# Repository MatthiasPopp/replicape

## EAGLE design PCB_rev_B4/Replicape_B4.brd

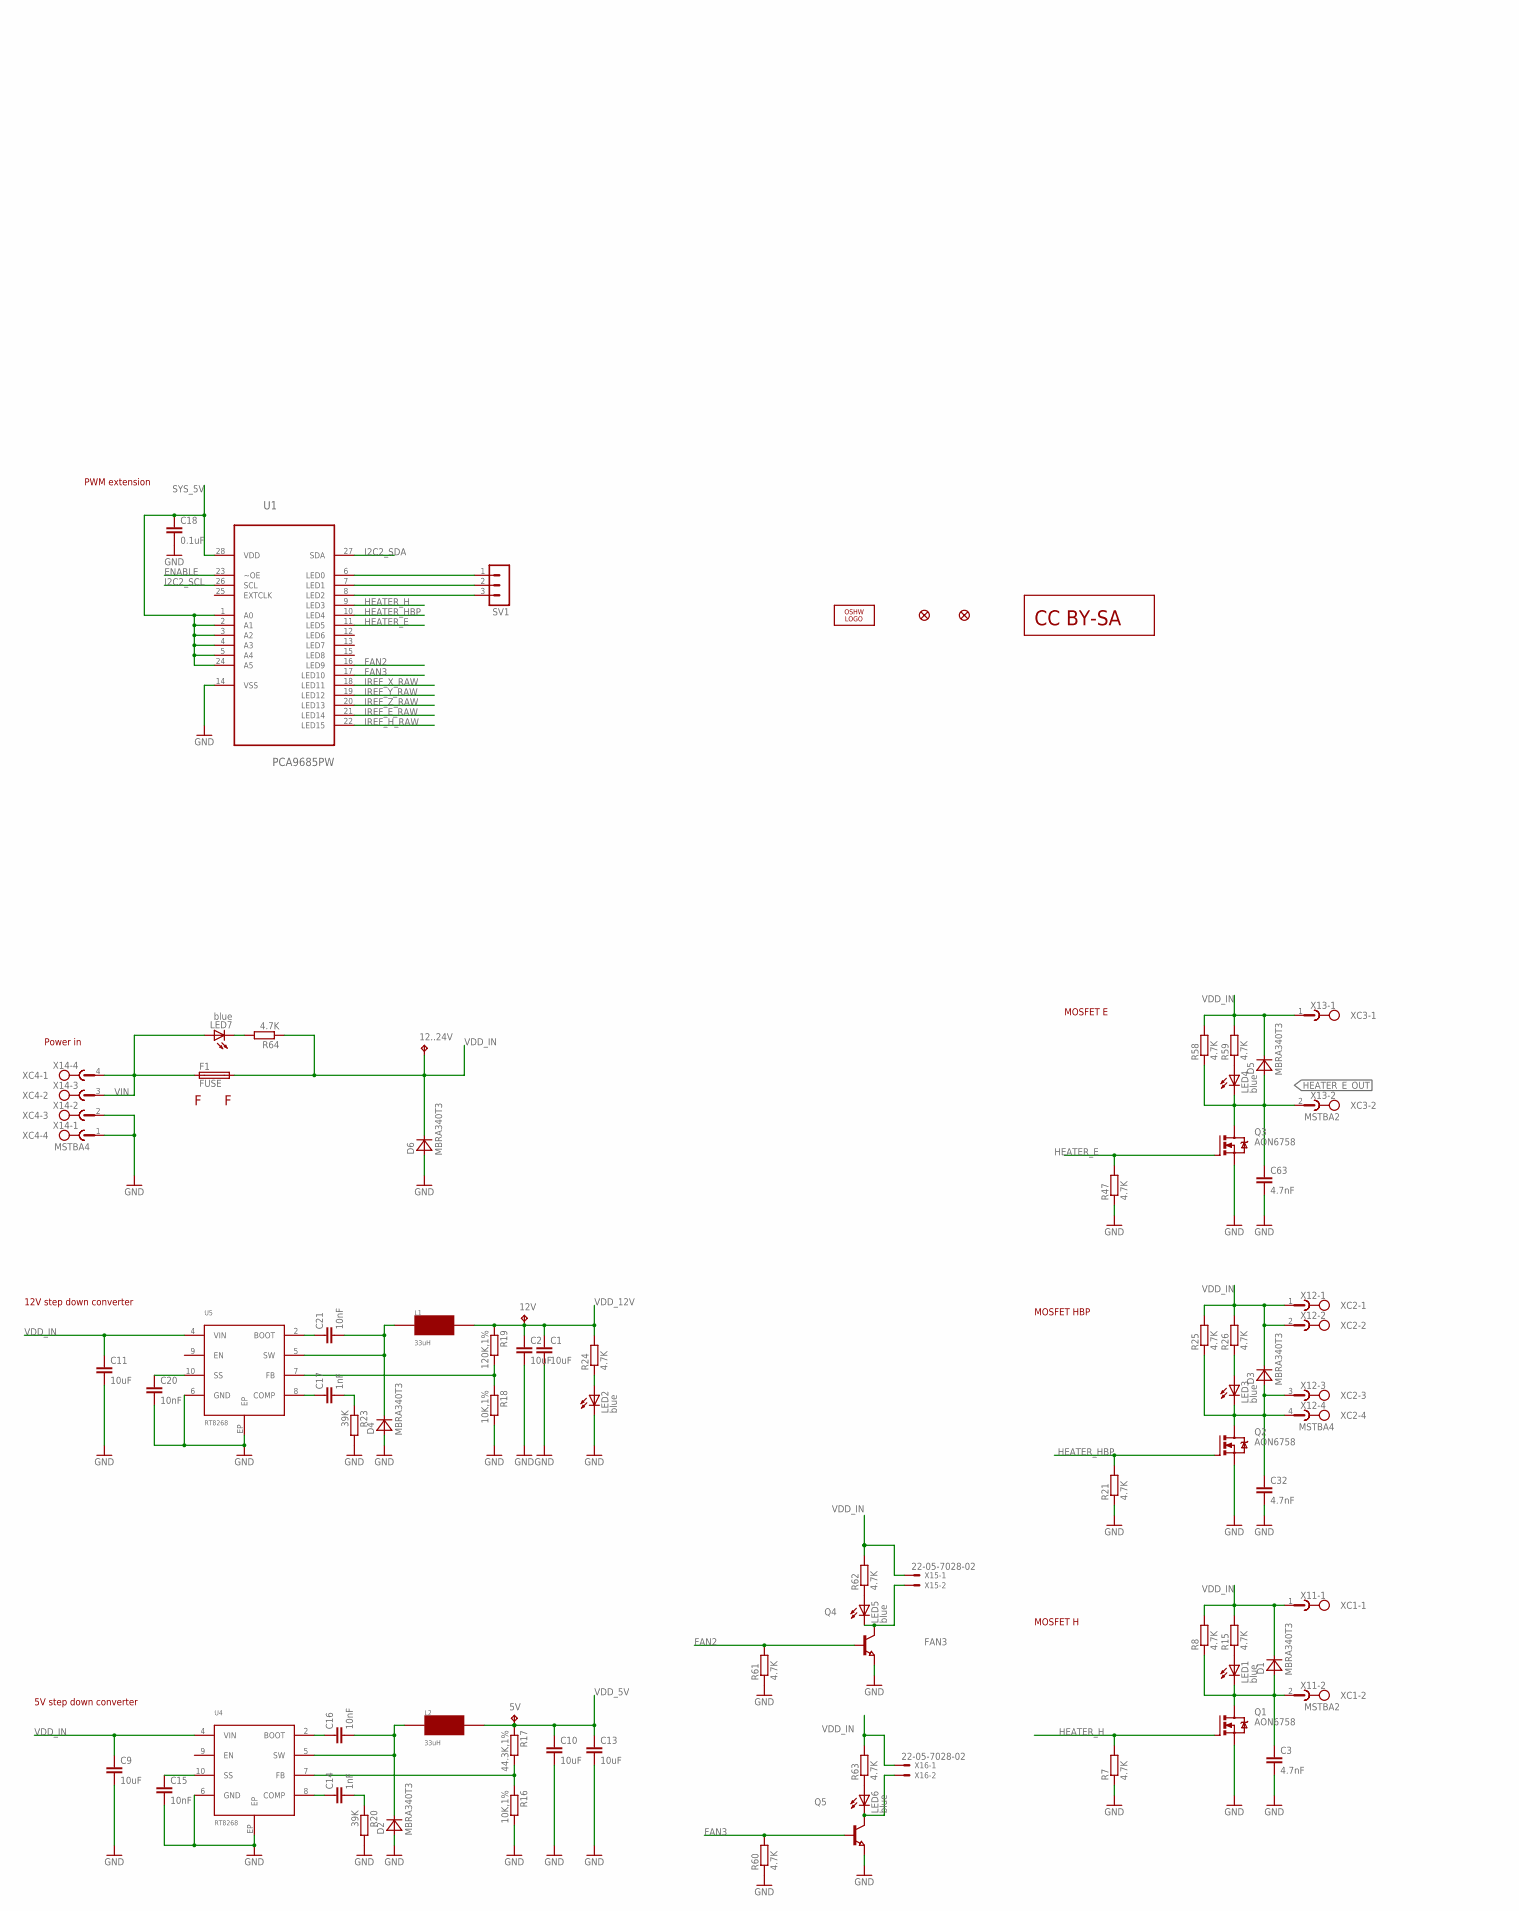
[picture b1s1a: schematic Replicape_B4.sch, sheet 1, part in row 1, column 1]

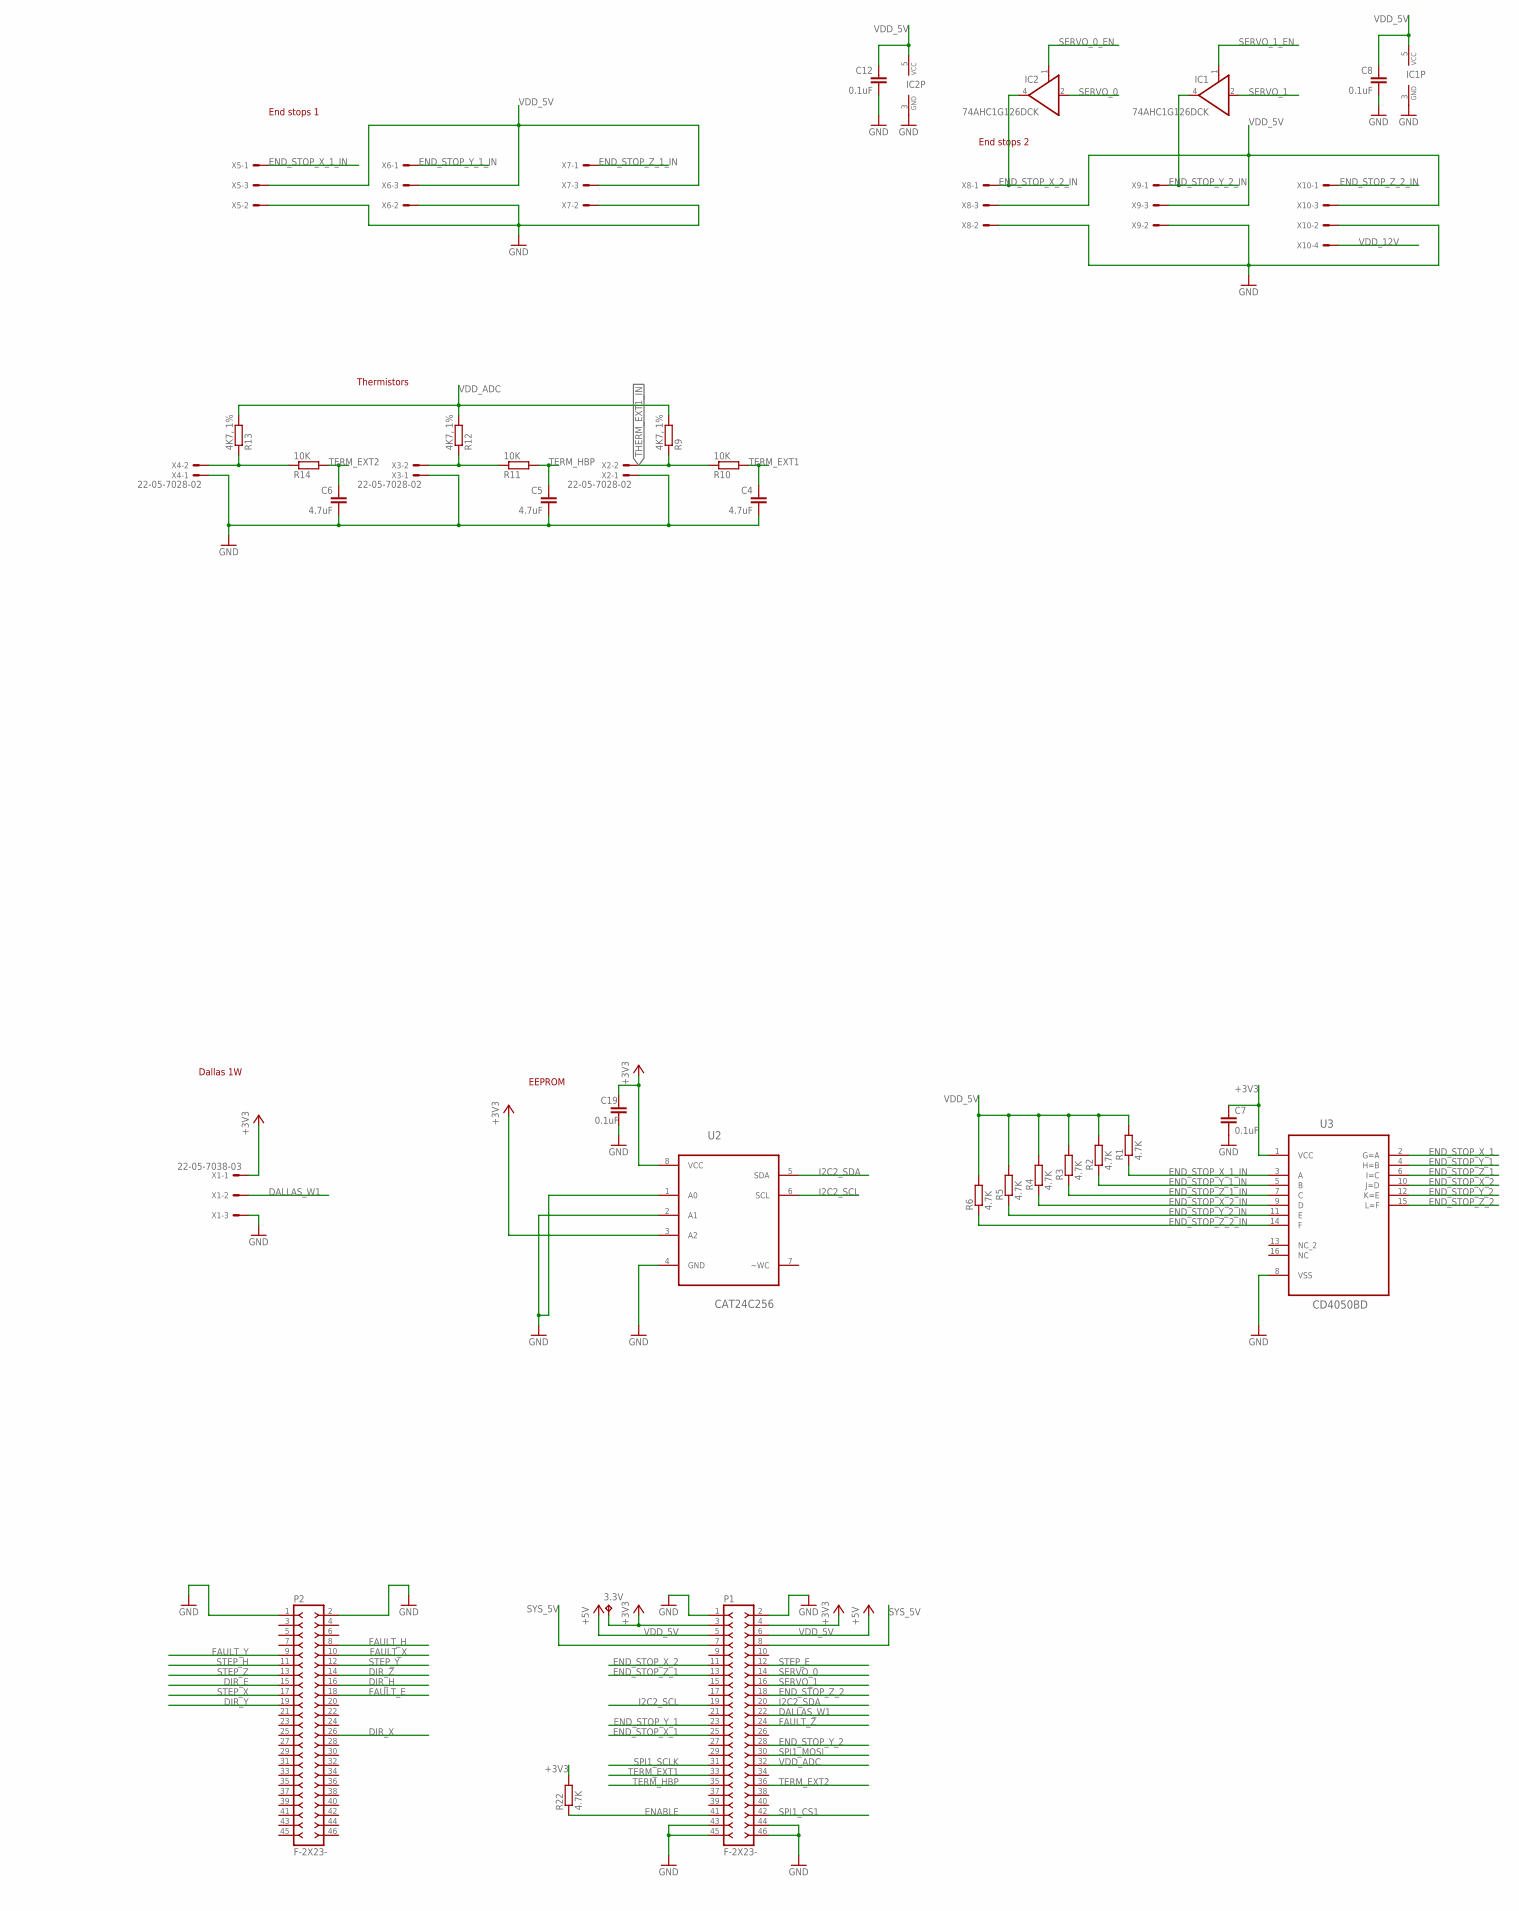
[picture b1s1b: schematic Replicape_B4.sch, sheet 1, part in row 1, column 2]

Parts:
3.3V, 5V, 12..24V, 12V: TPB1,27; B1,27
C1, C2, C9, C10, C11, C13: 10uF; C1206; MPN CL31B106KAHNNNE
C3, C32, C63: 4.7nF; C0402; MPN CL05B472KA5NNNC
C4, C5, C6: 4.7uF; C0402; MPN GRM155R60J475ME47D
C7, C8, C12, C18, C19: 0.1uF; C0402; MPN CL10B104KB8NNND
C14, C17: 1nF; C0402; MPN C1005X7R1H102K050BA
C15, C16, C20, C21: 10nF; C0402; MPN CL05B103KB5NNNC
D1, D2, D3, D4, D5, D6: MBRA340T3; SMA; MPN MBRA340T3G
F1: FUSE; 3557; MPN 0891020.NXS
FH1, FH2: FUSE-HOLDER; MPN 3557
IC1, IC2: 74AHC1G126DCK; SC70-5; MPN M74VHC1GT126DF1G
JP1, JP2: FIDUCIAL1X2.5; FIDUCIAL-1X2.5
L1, L2: 33uH; NR8040T330; MPN NR8040T330M
LED1, LED2, LED3, LED4, LED5, LED6, LED7: blue; CHIP-LED0603; MPN Q65110A7211
LOGO1: OSHW_LOGO_FILLX0200-NT; OSHW_FILLX200_NOTEXT
P1, P2: F-2X23-; DIL-100-2X23; MPN SSHQ-123-D-08-F-LF
Q1, Q2, Q3: AON6758; 8-DFN-EP-(5X6); MPN SIRA34DP-T1-GE3
Q4, Q5: NPN-TRANSISTOR_SOT23; SOT23; MPN AO7400
R1, R2, R3, R4, R5, R6, R7, R8, R15, R21, R22, R24, R25, R26, R47, R58, R59, R60, R61, R62, R63, R64: 4.7K; R0402; MPN RC0402JR-074K7L
R9, R12, R13: 4K7, 1%; R0402; MPN RC0402FR-074K7L
R10, R11, R14: 10K; R0402; MPN RC0402FR-0710KL
R16, R18: 10K,1%; R0402; MPN RC0402FR-0710KL
R17: 44.3K,1%; R0402; MPN RC1005F4422CS
R19: 120K,1%; R0402; MPN RMCF0402FT120K
R20, R23: 39K; R0402; MPN RC1005J393CS
SV1: MA03-1
U1: PCA9685PW; SOP65P640X110-28N; MPN PCA9685PW,112
U2: CAT24C256; SOIC127P600X175-8N; MPN CAT24C256WI-GT3
U3: CD4050BD; SOIC127P600X175-16N; MPN CD4050BDR
U4, U5: RT8268; MSOP10; MPN RT8268GFP
U$1: CC-BY-SA
X1, X5, X6, X7, X8, X9: 22-05-7038-03; 7395-03; MPN 640455-3
X2, X3, X4, X15, X16: 22-05-7028-02; 7395-02; MPN 640455-2
X10: 22-05-7048-04; 7395-04; MPN 640455-4
X11, X13: MSTBA2; MPN 39532-1002
X12, X14: MSTBA4; MPN 39532-1004
XC1, XC3: MSTBV2-CONNECTOR; MSTBA2-CONNECTOR; MPN 39530-0002
XC2, XC4: MSTBA4-CONNECTOR; MPN 39530-0004

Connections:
+3V3: 3.3V.TP, C7.1, C19.1, P1.3, P1.4, R22.2, U2.3 (A2), U2.8 (VCC), U3.1 (VCC), X1.1; also elsewhere on the board
DALLAS_W1: P1.22, X1.2
DIR_E: P2.15; also elsewhere on the board
DIR_H: P2.16; also elsewhere on the board
DIR_X: P2.26; also elsewhere on the board
DIR_Y: P2.19; also elsewhere on the board
DIR_Z: P2.14; also elsewhere on the board
ENABLE: P1.41, R22.1, U1.23 (~OE)
END_STOP_X_1: P1.25, U3.2 (G=A)
END_STOP_X_1_IN: R1.1, U3.3 (A), X5.1
END_STOP_X_2: P1.11, U3.10 (J=D)
END_STOP_X_2_IN: IC2.4 (O), R4.1, U3.9 (D), X8.1
END_STOP_Y_1: P1.23, U3.4 (H=B)
END_STOP_Y_1_IN: R2.1, U3.5 (B), X6.1
END_STOP_Y_2: P1.28, U3.12 (K=E)
END_STOP_Y_2_IN: IC1.4 (O), R5.1, U3.11 (E), X9.1
END_STOP_Z_1: P1.13, U3.6 (I=C)
END_STOP_Z_1_IN: R3.1, U3.7 (C), X7.1
END_STOP_Z_2: P1.18, U3.15 (L=F)
END_STOP_Z_2_IN: R6.1, U3.14 (F), X10.1
FAN2: Q4.1 (B), R61.2, U1.16 (LED9)
FAN3: Q5.1 (B), R60.2, U1.17 (LED10)
FAULT_E: P2.18; also elsewhere on the board
FAULT_H: P2.8; also elsewhere on the board
FAULT_X: P2.10; also elsewhere on the board
FAULT_Y: P2.9; also elsewhere on the board
FAULT_Z: P1.24; also elsewhere on the board
GND: C1.2, C2.2, C3.2, C4.2, C5.2, C6.2, C7.2, C8.2, C9.2, C10.2, C11.2, C12.2, C13.2, C15.2, C18.2, C19.2, C20.2, C32.2, C63.2, D2.A, D4.A, D6.A, IC1.3 (GND), IC2.3 (GND), LED2.C, P1.1, P1.2, P1.43, P1.44, P1.45, P1.46, P2.1, P2.2, Q1.1 (S), Q1.2 (S), Q1.3 (S), Q2.1 (S), Q2.2 (S), Q2.3 (S), Q3.1 (S), Q3.2 (S), Q3.3 (S), Q4.2 (E), Q5.2 (E), R7.1, R16.2, R18.2, R20.2, R21.1, R23.2, R47.1, R60.1, R61.1, U1.14 (VSS), U2.1 (A0), U2.2 (A1), U2.4 (GND), U3.8 (VSS), U4.6 (GND), U4.EP, U5.6 (GND), U5.EP, X1.3, X2.1, X3.1, X4.1, X5.2, X6.2, X7.2, X8.2, X9.2, X10.2, X14.1, X14.2; also elsewhere on the board
HEATER_E: Q3.4 (G), R47.2, U1.11 (LED5)
HEATER_E_OUT: C63.1, D5.A, LED4.C, Q3.5 (D), Q3.6 (D), Q3.7 (D), Q3.8 (D), Q3.TH (D), R58.1, X13.2
HEATER_H: Q1.4 (G), R7.2, U1.9 (LED3)
HEATER_HBP: Q2.4 (G), R21.2, U1.10 (LED4)
I2C2_SCL: P1.19, U1.26 (SCL), U2.6 (SCL)
I2C2_SDA: P1.20, U1.27 (SDA), U2.5 (SDA)
IREF_E_RAW: U1.21 (LED14); also elsewhere on the board
IREF_H_RAW: U1.22 (LED15); also elsewhere on the board
IREF_X_RAW: U1.18 (LED11); also elsewhere on the board
IREF_Y_RAW: U1.19 (LED12); also elsewhere on the board
IREF_Z_RAW: U1.20 (LED13); also elsewhere on the board
unnamed: SV1.1, U1.6 (LED0)
unnamed: LED7.C, R64.2
unnamed: R16.1, R17.2, U4.7 (FB)
unnamed: C16.2, D2.C, L2.P$2, U4.5 (SW)
unnamed: C15.1, U4.10 (SS)
unnamed: C3.1, D1.A, LED1.C, Q1.5 (D), Q1.6 (D), Q1.7 (D), Q1.8 (D), Q1.TH (D), R8.1, X11.2
unnamed: C16.1, U4.2 (BOOT)
unnamed: C14.1, U4.8 (COMP)
unnamed: LED2.A, R24.1
unnamed: C14.2, R20.1
unnamed: LED6.C, Q5.3 (C), X16.2
unnamed: LED5.C, Q4.3 (C), X15.2
unnamed: LED5.A, R62.1
unnamed: LED6.A, R63.1
unnamed: SV1.3, U1.8 (LED2)
unnamed: SV1.2, U1.7 (LED1)
unnamed: LED4.A, R59.1
unnamed: LED1.A, R15.1
unnamed: LED3.A, R26.1
unnamed: R18.1, R19.2, U5.7 (FB)
unnamed: C21.2, D4.C, L1.P$2, U5.5 (SW)
unnamed: R13.1, R14.1, X4.2
unnamed: R11.1, R12.1, X3.2
unnamed: C32.1, D3.A, LED3.C, Q2.5 (D), Q2.6 (D), Q2.7 (D), Q2.8 (D), Q2.TH (D), R25.1, X12.3, X12.4
unnamed: C20.1, U5.10 (SS)
unnamed: C17.1, U5.8 (COMP)
unnamed: C21.1, U5.2 (BOOT)
unnamed: C17.2, R23.1
SERVO_0: IC2.2 (I), P1.14
SERVO_0_EN: IC2.1 (OE); also elsewhere on the board
SERVO_1: IC1.2 (I), P1.16
SERVO_1_EN: IC1.1 (OE); also elsewhere on the board
SPI1_CS1: P1.42; also elsewhere on the board
SPI1_MOSI: P1.30; also elsewhere on the board
SPI1_SCLK: P1.31; also elsewhere on the board
STEP_E: P1.12; also elsewhere on the board
STEP_H: P2.11; also elsewhere on the board
STEP_X: P2.17; also elsewhere on the board
STEP_Y: P2.12; also elsewhere on the board
STEP_Z: P2.13; also elsewhere on the board
SYS_5V: C18.1, P1.7, P1.8, U1.1 (A0), U1.2 (A1), U1.3 (A2), U1.4 (A3), U1.5 (A4), U1.24 (A5), U1.28 (VDD)
TERM_EXT1: C4.1, P1.33, R10.2
TERM_EXT2: C6.1, P1.36, R14.2
TERM_HBP: C5.1, P1.35, R11.2
THERM_EXT1_IN: R9.1, R10.1, X2.2
VDD_5V: 5V.TP, C8.1, C10.1, C12.1, C13.1, IC1.5 (VCC), IC2.5 (VCC), L2.P$1, P1.5, P1.6, R1.2, R2.2, R3.2, R4.2, R5.2, R6.2, R17.1, X5.3, X6.3, X7.3, X8.3, X9.3, X10.3
VDD_12V: 12V.TP, C1.1, C2.1, L1.P$1, R19.1, R24.2, X10.4
VDD_ADC: P1.32, R9.2, R12.2, R13.2
VDD_IN: 12..24V.TP, C9.1, C11.1, D1.C, D3.C, D5.C, D6.C, F1.P$3 (2), F1.P$4 (2), R8.2, R15.2, R25.2, R26.2, R58.2, R59.2, R62.2, R63.2, R64.1, U4.4 (VIN), U5.4 (VIN), X11.1, X12.1, X12.2, X13.1, X15.1, X16.1; also elsewhere on the board
VIN: F1.P$1 (1), F1.P$2 (1), LED7.A, X14.3, X14.4

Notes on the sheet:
PWM extension
Power in
5V step down converter
12V step down converter
MOSFET E
MOSFET HBP
MOSFET H
End stops 2
Thermistors
End stops 1
EEPROM
Dallas 1W

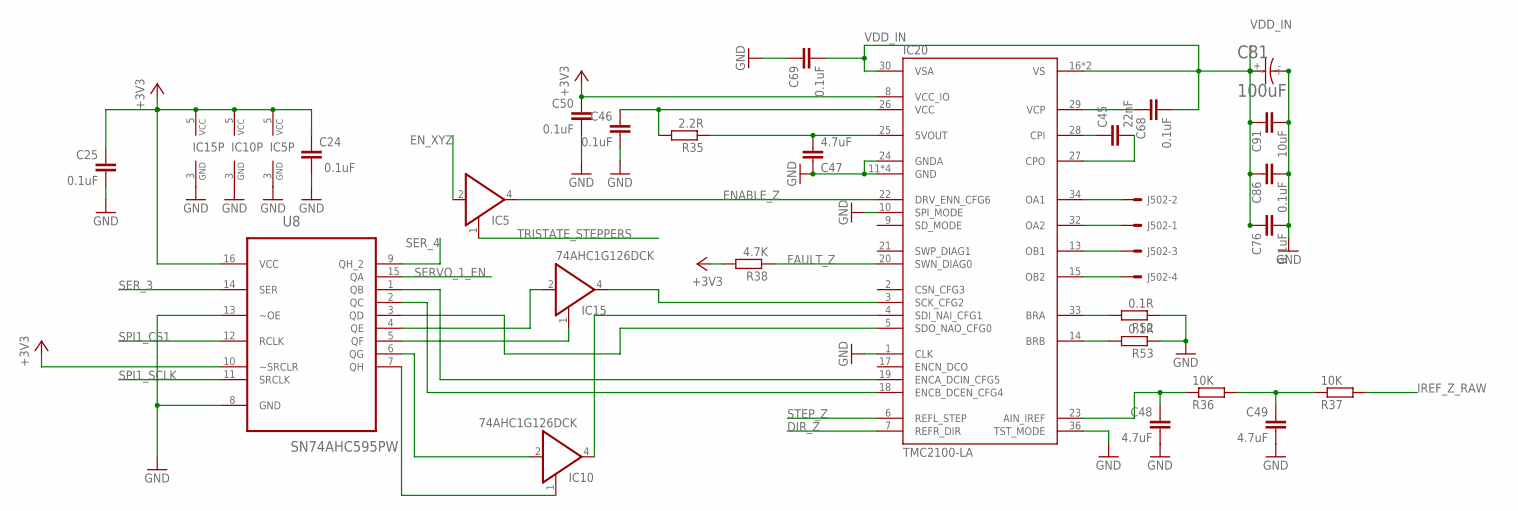
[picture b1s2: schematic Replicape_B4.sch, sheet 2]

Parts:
C24, C25, C46, C50, C68, C69, C76, C86: 0.1uF; C0402; MPN CL10B104KB8NNND
C45: 22nF; C0402; MPN C1005X7R1E223K050BB
C47, C48, C49: 4.7uF; C0402; MPN GRM155R60J475ME47D
C81: 100uF; RHS1V10MCN1GS; MPN RHS1V101MCN1GS
C91: 10uF; C0805; MPN C2012X5R1V106M085AC
IC5, IC10, IC15: 74AHC1G126DCK; SC70-5; MPN M74VHC1GT126DF1G
IC20: TMC2100-LA; QFN36-PAD; MPN TMC2100-LA-T
J502: 22-05-7048-04; 7395-04; MPN 640455-4
R35: 2.2R; R0402; MPN RC1005J2R2CS
R36, R37: 10K; R0402; MPN RC0402FR-0710KL
R38: 4.7K; R0402; MPN RC0402JR-074K7L
R52, R53: 0.1R; R0805; MPN RL1220S-R10-F
U8: SN74AHC595PW; SOP65P640X120-16N; MPN MC74HC595ADTR2G

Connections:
+3V3: C24.1, C25.1, C50.1, IC5.5 (VCC), IC10.5 (VCC), IC15.5 (VCC), IC20.8 (VCC_IO), R38.2, U8.10 (~SRCLR), U8.16 (VCC); also elsewhere on the board
DIR_Z: IC20.7 (REFR_DIR); also elsewhere on the board
ENABLE_Z: IC5.4 (O), IC20.22 (DRV_ENN_CFG6)
EN_XYZ: IC5.2 (I); also elsewhere on the board
FAULT_Z: IC20.20 (SWN_DIAG0), R38.1; also elsewhere on the board
GND: C24.2, C25.2, C46.2, C47.1, C48.2, C49.2, C50.2, C69.1, C76.2, C81.-, C86.2, C91.2, IC5.3 (GND), IC10.3 (GND), IC15.3 (GND), IC20.1 (CLK), IC20.10 (SPI_MODE), IC20.11 (GND), IC20.12 (GND), IC20.24 (GNDA), IC20.35 (GND), IC20.36 (TST_MODE), IC20.TP (GND), R52.1, R53.1, U8.8 (GND), U8.13 (~OE); also elsewhere on the board
IREF_Z6: C49.1, R36.2, R37.1
IREF_Z_RAW: R37.2; also elsewhere on the board
unnamed: C45.2, IC20.27 (CPO)
unnamed: IC20.14 (BRB), R53.2
unnamed: IC20.33 (BRA), R52.2
unnamed: C48.1, IC20.23 (AIN_IREF), R36.1
unnamed: C45.1, IC20.28 (CPI)
unnamed: IC15.4 (O), IC20.3 (SCK_CFG2)
unnamed: C47.2, IC20.25 (5VOUT), R35.1
unnamed: C68.1, IC20.29 (VCP)
unnamed: IC10.4 (O), IC20.4 (SDI_NAI_CFG1)
unnamed: IC20.5 (SDO_NAO_CFG0), U8.3 (QD)
unnamed: IC20.18 (ENCB_DCEN_CFG4), U8.2 (QC)
unnamed: IC20.19 (ENCA_DCIN_CFG5), U8.1 (QB)
unnamed: IC10.1 (OE), U8.7 (QH)
unnamed: IC10.2 (I), U8.6 (QG)
unnamed: IC15.2 (I), U8.4 (QE)
unnamed: IC15.1 (OE), U8.5 (QF)
unnamed: C46.1, IC20.26 (VCC), R35.2
unnamed: IC20.15 (OB2), J502.4
unnamed: IC20.34 (OA1), J502.2
unnamed: IC20.32 (OA2), J502.1
unnamed: IC20.13 (OB1), J502.3
SERVO_1_EN: U8.15 (QA); also elsewhere on the board
SER_3: U8.14 (SER); also elsewhere on the board
SER_4: U8.9 (QH_2); also elsewhere on the board
SPI1_CS1: U8.12 (RCLK); also elsewhere on the board
SPI1_SCLK: U8.11 (SRCLK); also elsewhere on the board
STEP_Z: IC20.6 (REFL_STEP); also elsewhere on the board
TRISTATE_STEPPERS: IC5.1 (OE); also elsewhere on the board
VDD_IN: C68.2, C69.2, C76.1, C81.+, C86.1, C91.1, IC20.16 (VS), IC20.30 (VSA), IC20.31 (VS); also elsewhere on the board

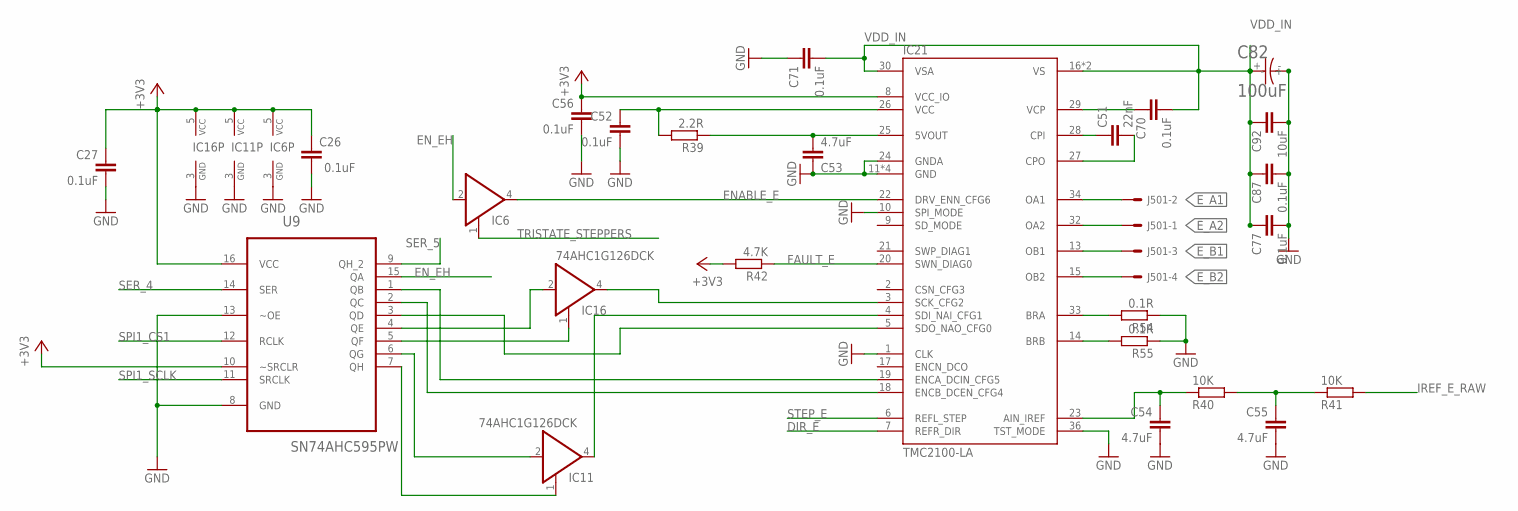
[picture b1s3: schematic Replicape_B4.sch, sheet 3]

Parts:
C26, C27, C52, C56, C70, C71, C77, C87: 0.1uF; C0402; MPN CL10B104KB8NNND
C51: 22nF; C0402; MPN C1005X7R1E223K050BB
C53, C54, C55: 4.7uF; C0402; MPN GRM155R60J475ME47D
C82: 100uF; RHS1V10MCN1GS; MPN RHS1V101MCN1GS
C92: 10uF; C0805; MPN C2012X5R1V106M085AC
IC6, IC11, IC16: 74AHC1G126DCK; SC70-5; MPN M74VHC1GT126DF1G
IC21: TMC2100-LA; QFN36-PAD; MPN TMC2100-LA-T
J501: 22-05-7048-04; 7395-04; MPN 640455-4
R39: 2.2R; R0402; MPN RC1005J2R2CS
R40, R41: 10K; R0402; MPN RC0402FR-0710KL
R42: 4.7K; R0402; MPN RC0402JR-074K7L
R54, R55: 0.1R; R0805; MPN RL1220S-R10-F
U9: SN74AHC595PW; SOP65P640X120-16N; MPN MC74HC595ADTR2G

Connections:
+3V3: C26.1, C27.1, C56.1, IC6.5 (VCC), IC11.5 (VCC), IC16.5 (VCC), IC21.8 (VCC_IO), R42.2, U9.10 (~SRCLR), U9.16 (VCC); also elsewhere on the board
DIR_E: IC21.7 (REFR_DIR); also elsewhere on the board
ENABLE_E: IC6.4 (O), IC21.22 (DRV_ENN_CFG6)
EN_EH: IC6.2 (I), U9.15 (QA); also elsewhere on the board
E_A1: IC21.34 (OA1), J501.2
E_A2: IC21.32 (OA2), J501.1
E_B1: IC21.13 (OB1), J501.3
E_B2: IC21.15 (OB2), J501.4
FAULT_E: IC21.20 (SWN_DIAG0), R42.1; also elsewhere on the board
GND: C26.2, C27.2, C52.2, C53.1, C54.2, C55.2, C56.2, C71.1, C77.2, C82.-, C87.2, C92.2, IC6.3 (GND), IC11.3 (GND), IC16.3 (GND), IC21.1 (CLK), IC21.10 (SPI_MODE), IC21.11 (GND), IC21.12 (GND), IC21.24 (GNDA), IC21.35 (GND), IC21.36 (TST_MODE), IC21.TP (GND), R54.1, R55.1, U9.8 (GND), U9.13 (~OE); also elsewhere on the board
IREF_E_RAW: R41.2; also elsewhere on the board
IREF_Z7: C55.1, R40.2, R41.1
unnamed: C51.2, IC21.27 (CPO)
unnamed: IC21.14 (BRB), R55.2
unnamed: IC21.33 (BRA), R54.2
unnamed: C54.1, IC21.23 (AIN_IREF), R40.1
unnamed: C51.1, IC21.28 (CPI)
unnamed: IC16.4 (O), IC21.3 (SCK_CFG2)
unnamed: C53.2, IC21.25 (5VOUT), R39.1
unnamed: C70.1, IC21.29 (VCP)
unnamed: IC11.4 (O), IC21.4 (SDI_NAI_CFG1)
unnamed: IC21.5 (SDO_NAO_CFG0), U9.3 (QD)
unnamed: IC21.18 (ENCB_DCEN_CFG4), U9.2 (QC)
unnamed: IC21.19 (ENCA_DCIN_CFG5), U9.1 (QB)
unnamed: IC11.1 (OE), U9.7 (QH)
unnamed: IC11.2 (I), U9.6 (QG)
unnamed: IC16.2 (I), U9.4 (QE)
unnamed: IC16.1 (OE), U9.5 (QF)
unnamed: C52.1, IC21.26 (VCC), R39.2
SER_4: U9.14 (SER); also elsewhere on the board
SER_5: U9.9 (QH_2); also elsewhere on the board
SPI1_CS1: U9.12 (RCLK); also elsewhere on the board
SPI1_SCLK: U9.11 (SRCLK); also elsewhere on the board
STEP_E: IC21.6 (REFL_STEP); also elsewhere on the board
TRISTATE_STEPPERS: IC6.1 (OE); also elsewhere on the board
VDD_IN: C70.2, C71.2, C77.1, C82.+, C87.1, C92.1, IC21.16 (VS), IC21.30 (VSA), IC21.31 (VS); also elsewhere on the board

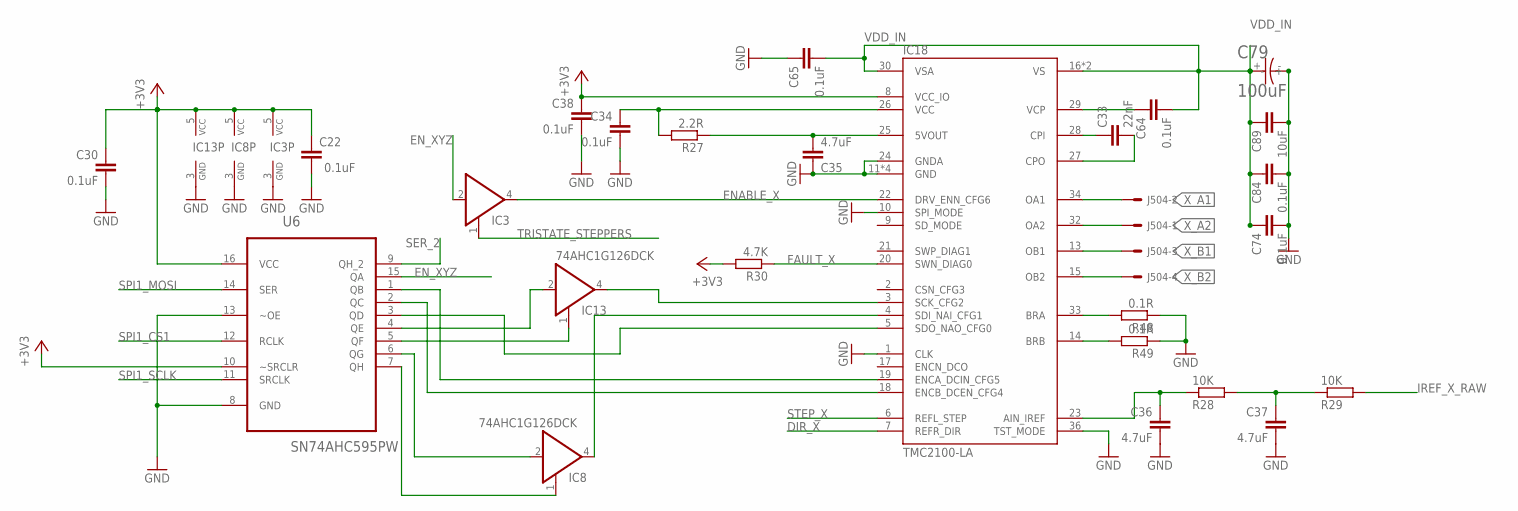
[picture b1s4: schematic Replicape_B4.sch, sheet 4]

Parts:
C22, C30, C34, C38, C64, C65, C74, C84: 0.1uF; C0402; MPN CL10B104KB8NNND
C33: 22nF; C0402; MPN C1005X7R1E223K050BB
C35, C36, C37: 4.7uF; C0402; MPN GRM155R60J475ME47D
C79: 100uF; RHS1V10MCN1GS; MPN RHS1V101MCN1GS
C89: 10uF; C0805; MPN C2012X5R1V106M085AC
IC3, IC8, IC13: 74AHC1G126DCK; SC70-5; MPN M74VHC1GT126DF1G
IC18: TMC2100-LA; QFN36-PAD; MPN TMC2100-LA-T
J504: 22-05-7048-04; 7395-04; MPN 640455-4
R27: 2.2R; R0402; MPN RC1005J2R2CS
R28, R29: 10K; R0402; MPN RC0402FR-0710KL
R30: 4.7K; R0402; MPN RC0402JR-074K7L
R48, R49: 0.1R; R0805; MPN RL1220S-R10-F
U6: SN74AHC595PW; SOP65P640X120-16N; MPN MC74HC595ADTR2G

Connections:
+3V3: C22.1, C30.1, C38.1, IC3.5 (VCC), IC8.5 (VCC), IC13.5 (VCC), IC18.8 (VCC_IO), R30.2, U6.10 (~SRCLR), U6.16 (VCC); also elsewhere on the board
DIR_X: IC18.7 (REFR_DIR); also elsewhere on the board
ENABLE_X: IC3.4 (O), IC18.22 (DRV_ENN_CFG6)
EN_XYZ: IC3.2 (I), U6.15 (QA); also elsewhere on the board
FAULT_X: IC18.20 (SWN_DIAG0), R30.1; also elsewhere on the board
GND: C22.2, C30.2, C34.2, C35.1, C36.2, C37.2, C38.2, C65.1, C74.2, C79.-, C84.2, C89.2, IC3.3 (GND), IC8.3 (GND), IC13.3 (GND), IC18.1 (CLK), IC18.10 (SPI_MODE), IC18.11 (GND), IC18.12 (GND), IC18.24 (GNDA), IC18.35 (GND), IC18.36 (TST_MODE), IC18.TP (GND), R48.1, R49.1, U6.8 (GND), U6.13 (~OE); also elsewhere on the board
IREF_X_RAW: R29.2; also elsewhere on the board
IREF_Z8: C37.1, R28.2, R29.1
unnamed: C33.2, IC18.27 (CPO)
unnamed: IC18.14 (BRB), R49.2
unnamed: IC18.33 (BRA), R48.2
unnamed: C36.1, IC18.23 (AIN_IREF), R28.1
unnamed: C33.1, IC18.28 (CPI)
unnamed: IC13.4 (O), IC18.3 (SCK_CFG2)
unnamed: C35.2, IC18.25 (5VOUT), R27.1
unnamed: C64.1, IC18.29 (VCP)
unnamed: IC8.4 (O), IC18.4 (SDI_NAI_CFG1)
unnamed: IC18.5 (SDO_NAO_CFG0), U6.3 (QD)
unnamed: IC18.18 (ENCB_DCEN_CFG4), U6.2 (QC)
unnamed: IC18.19 (ENCA_DCIN_CFG5), U6.1 (QB)
unnamed: IC8.1 (OE), U6.7 (QH)
unnamed: IC8.2 (I), U6.6 (QG)
unnamed: IC13.2 (I), U6.4 (QE)
unnamed: IC13.1 (OE), U6.5 (QF)
unnamed: C34.1, IC18.26 (VCC), R27.2
SER_2: U6.9 (QH_2); also elsewhere on the board
SPI1_CS1: U6.12 (RCLK); also elsewhere on the board
SPI1_MOSI: U6.14 (SER); also elsewhere on the board
SPI1_SCLK: U6.11 (SRCLK); also elsewhere on the board
STEP_X: IC18.6 (REFL_STEP); also elsewhere on the board
TRISTATE_STEPPERS: IC3.1 (OE); also elsewhere on the board
VDD_IN: C64.2, C65.2, C74.1, C79.+, C84.1, C89.1, IC18.16 (VS), IC18.30 (VSA), IC18.31 (VS); also elsewhere on the board
X_A1: IC18.34 (OA1), J504.2
X_A2: IC18.32 (OA2), J504.1
X_B1: IC18.13 (OB1), J504.3
X_B2: IC18.15 (OB2), J504.4

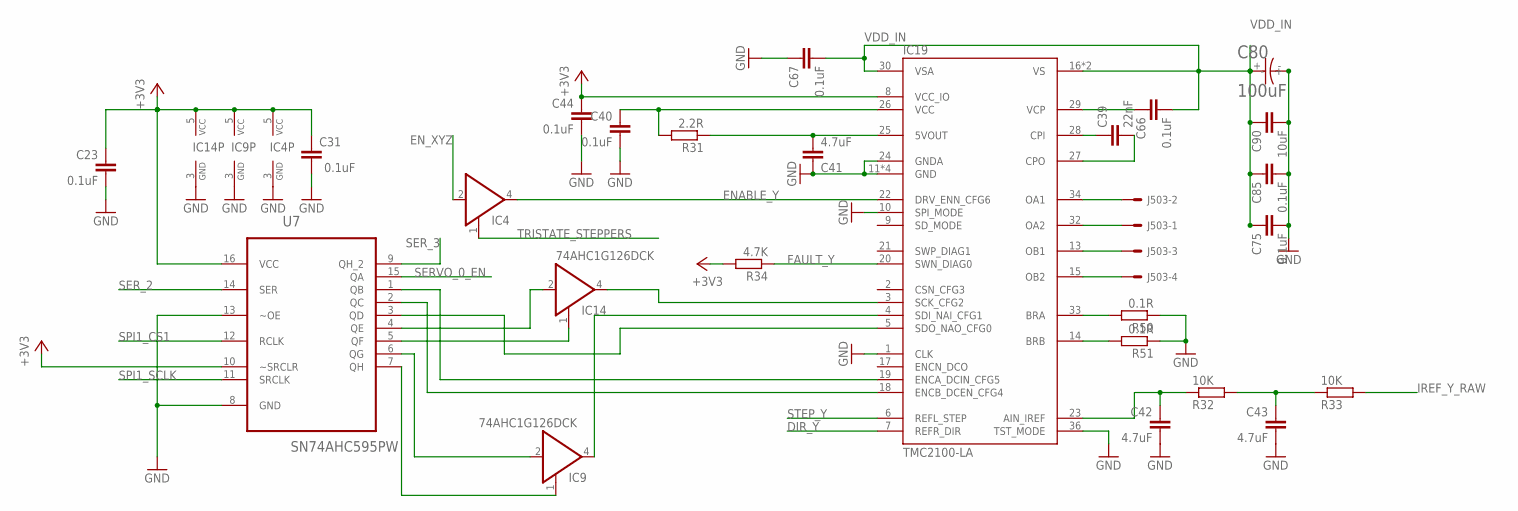
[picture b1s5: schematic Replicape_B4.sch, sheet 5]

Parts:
C23, C31, C40, C44, C66, C67, C75, C85: 0.1uF; C0402; MPN CL10B104KB8NNND
C39: 22nF; C0402; MPN C1005X7R1E223K050BB
C41, C42, C43: 4.7uF; C0402; MPN GRM155R60J475ME47D
C80: 100uF; RHS1V10MCN1GS; MPN RHS1V101MCN1GS
C90: 10uF; C0805; MPN C2012X5R1V106M085AC
IC4, IC9, IC14: 74AHC1G126DCK; SC70-5; MPN M74VHC1GT126DF1G
IC19: TMC2100-LA; QFN36-PAD; MPN TMC2100-LA-T
J503: 22-05-7048-04; 7395-04; MPN 640455-4
R31: 2.2R; R0402; MPN RC1005J2R2CS
R32, R33: 10K; R0402; MPN RC0402FR-0710KL
R34: 4.7K; R0402; MPN RC0402JR-074K7L
R50, R51: 0.1R; R0805; MPN RL1220S-R10-F
U7: SN74AHC595PW; SOP65P640X120-16N; MPN MC74HC595ADTR2G

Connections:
+3V3: C23.1, C31.1, C44.1, IC4.5 (VCC), IC9.5 (VCC), IC14.5 (VCC), IC19.8 (VCC_IO), R34.2, U7.10 (~SRCLR), U7.16 (VCC); also elsewhere on the board
DIR_Y: IC19.7 (REFR_DIR); also elsewhere on the board
ENABLE_Y: IC4.4 (O), IC19.22 (DRV_ENN_CFG6)
EN_XYZ: IC4.2 (I); also elsewhere on the board
FAULT_Y: IC19.20 (SWN_DIAG0), R34.1; also elsewhere on the board
GND: C23.2, C31.2, C40.2, C41.1, C42.2, C43.2, C44.2, C67.1, C75.2, C80.-, C85.2, C90.2, IC4.3 (GND), IC9.3 (GND), IC14.3 (GND), IC19.1 (CLK), IC19.10 (SPI_MODE), IC19.11 (GND), IC19.12 (GND), IC19.24 (GNDA), IC19.35 (GND), IC19.36 (TST_MODE), IC19.TP (GND), R50.1, R51.1, U7.8 (GND), U7.13 (~OE); also elsewhere on the board
IREF_Y_RAW: R33.2; also elsewhere on the board
IREF_Z9: C43.1, R32.2, R33.1
unnamed: C39.2, IC19.27 (CPO)
unnamed: IC19.14 (BRB), R51.2
unnamed: IC19.33 (BRA), R50.2
unnamed: C42.1, IC19.23 (AIN_IREF), R32.1
unnamed: C39.1, IC19.28 (CPI)
unnamed: IC14.4 (O), IC19.3 (SCK_CFG2)
unnamed: IC19.15 (OB2), J503.4
unnamed: IC19.34 (OA1), J503.2
unnamed: C41.2, IC19.25 (5VOUT), R31.1
unnamed: C66.1, IC19.29 (VCP)
unnamed: IC9.4 (O), IC19.4 (SDI_NAI_CFG1)
unnamed: IC19.5 (SDO_NAO_CFG0), U7.3 (QD)
unnamed: IC19.18 (ENCB_DCEN_CFG4), U7.2 (QC)
unnamed: IC19.19 (ENCA_DCIN_CFG5), U7.1 (QB)
unnamed: IC9.1 (OE), U7.7 (QH)
unnamed: IC9.2 (I), U7.6 (QG)
unnamed: IC14.2 (I), U7.4 (QE)
unnamed: IC14.1 (OE), U7.5 (QF)
unnamed: C40.1, IC19.26 (VCC), R31.2
unnamed: IC19.32 (OA2), J503.1
unnamed: IC19.13 (OB1), J503.3
SERVO_0_EN: U7.15 (QA); also elsewhere on the board
SER_2: U7.14 (SER); also elsewhere on the board
SER_3: U7.9 (QH_2); also elsewhere on the board
SPI1_CS1: U7.12 (RCLK); also elsewhere on the board
SPI1_SCLK: U7.11 (SRCLK); also elsewhere on the board
STEP_Y: IC19.6 (REFL_STEP); also elsewhere on the board
TRISTATE_STEPPERS: IC4.1 (OE); also elsewhere on the board
VDD_IN: C66.2, C67.2, C75.1, C80.+, C85.1, C90.1, IC19.16 (VS), IC19.30 (VSA), IC19.31 (VS); also elsewhere on the board

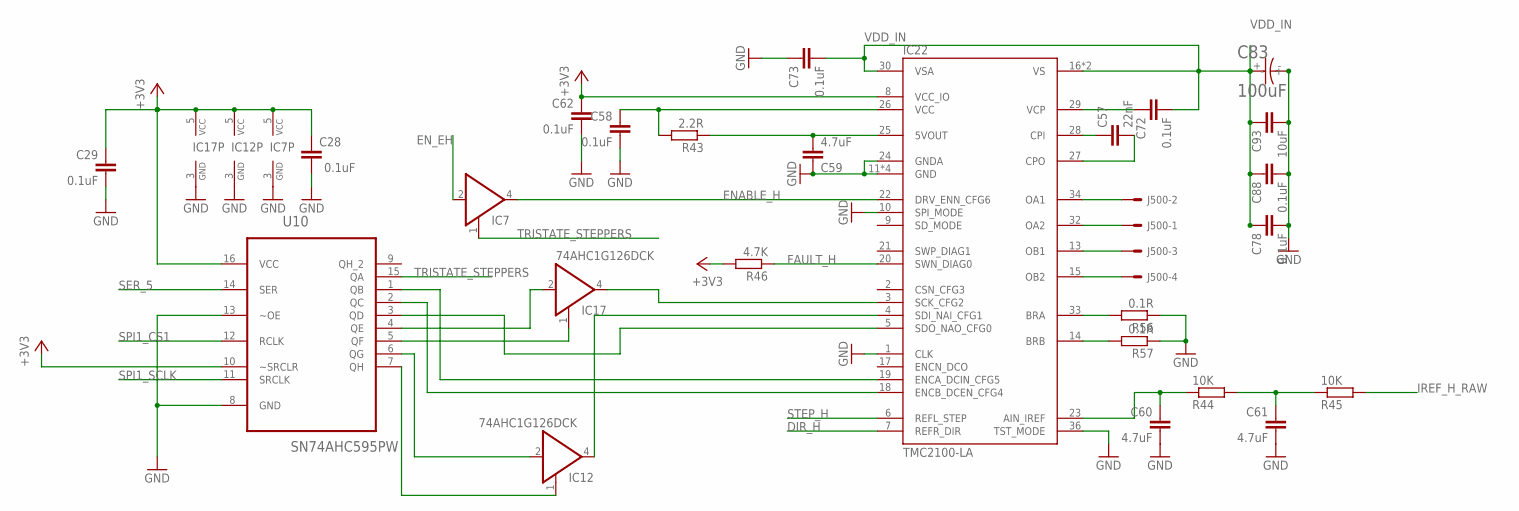
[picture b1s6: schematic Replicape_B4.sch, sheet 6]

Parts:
C28, C29, C58, C62, C72, C73, C78, C88: 0.1uF; C0402; MPN CL10B104KB8NNND
C57: 22nF; C0402; MPN C1005X7R1E223K050BB
C59, C60, C61: 4.7uF; C0402; MPN GRM155R60J475ME47D
C83: 100uF; RHS1V10MCN1GS; MPN RHS1V101MCN1GS
C93: 10uF; C0805; MPN C2012X5R1V106M085AC
IC7, IC12, IC17: 74AHC1G126DCK; SC70-5; MPN M74VHC1GT126DF1G
IC22: TMC2100-LA; QFN36-PAD; MPN TMC2100-LA-T
J500: 22-05-7048-04; 7395-04; MPN 640455-4
R43: 2.2R; R0402; MPN RC1005J2R2CS
R44, R45: 10K; R0402; MPN RC0402FR-0710KL
R46: 4.7K; R0402; MPN RC0402JR-074K7L
R56, R57: 0.1R; R0805; MPN RL1220S-R10-F
U10: SN74AHC595PW; SOP65P640X120-16N; MPN MC74HC595ADTR2G

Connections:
+3V3: C28.1, C29.1, C62.1, IC7.5 (VCC), IC12.5 (VCC), IC17.5 (VCC), IC22.8 (VCC_IO), R46.2, U10.10 (~SRCLR), U10.16 (VCC); also elsewhere on the board
DIR_H: IC22.7 (REFR_DIR); also elsewhere on the board
ENABLE_H: IC7.4 (O), IC22.22 (DRV_ENN_CFG6)
EN_EH: IC7.2 (I); also elsewhere on the board
FAULT_H: IC22.20 (SWN_DIAG0), R46.1; also elsewhere on the board
GND: C28.2, C29.2, C58.2, C59.1, C60.2, C61.2, C62.2, C73.1, C78.2, C83.-, C88.2, C93.2, IC7.3 (GND), IC12.3 (GND), IC17.3 (GND), IC22.1 (CLK), IC22.10 (SPI_MODE), IC22.11 (GND), IC22.12 (GND), IC22.24 (GNDA), IC22.35 (GND), IC22.36 (TST_MODE), IC22.TP (GND), R56.1, R57.1, U10.8 (GND), U10.13 (~OE); also elsewhere on the board
IREF_H_RAW: R45.2; also elsewhere on the board
IREF_Z10: C61.1, R44.2, R45.1
unnamed: C57.2, IC22.27 (CPO)
unnamed: IC22.14 (BRB), R57.2
unnamed: IC22.33 (BRA), R56.2
unnamed: C60.1, IC22.23 (AIN_IREF), R44.1
unnamed: C57.1, IC22.28 (CPI)
unnamed: IC17.4 (O), IC22.3 (SCK_CFG2)
unnamed: IC22.15 (OB2), J500.4
unnamed: IC22.34 (OA1), J500.2
unnamed: C59.2, IC22.25 (5VOUT), R43.1
unnamed: C72.1, IC22.29 (VCP)
unnamed: IC12.4 (O), IC22.4 (SDI_NAI_CFG1)
unnamed: IC22.5 (SDO_NAO_CFG0), U10.3 (QD)
unnamed: IC22.18 (ENCB_DCEN_CFG4), U10.2 (QC)
unnamed: IC22.19 (ENCA_DCIN_CFG5), U10.1 (QB)
unnamed: IC12.1 (OE), U10.7 (QH)
unnamed: IC12.2 (I), U10.6 (QG)
unnamed: IC17.2 (I), U10.4 (QE)
unnamed: IC17.1 (OE), U10.5 (QF)
unnamed: C58.1, IC22.26 (VCC), R43.2
unnamed: IC22.32 (OA2), J500.1
unnamed: IC22.13 (OB1), J500.3
SER_5: U10.14 (SER); also elsewhere on the board
SPI1_CS1: U10.12 (RCLK); also elsewhere on the board
SPI1_SCLK: U10.11 (SRCLK); also elsewhere on the board
STEP_H: IC22.6 (REFL_STEP); also elsewhere on the board
TRISTATE_STEPPERS: IC7.1 (OE), U10.15 (QA); also elsewhere on the board
VDD_IN: C72.2, C73.2, C78.1, C83.+, C88.1, C93.1, IC22.16 (VS), IC22.30 (VSA), IC22.31 (VS); also elsewhere on the board

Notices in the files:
parts and their libraries:
con-headers-jp: Copyright (C) 2008, Bob Starr
